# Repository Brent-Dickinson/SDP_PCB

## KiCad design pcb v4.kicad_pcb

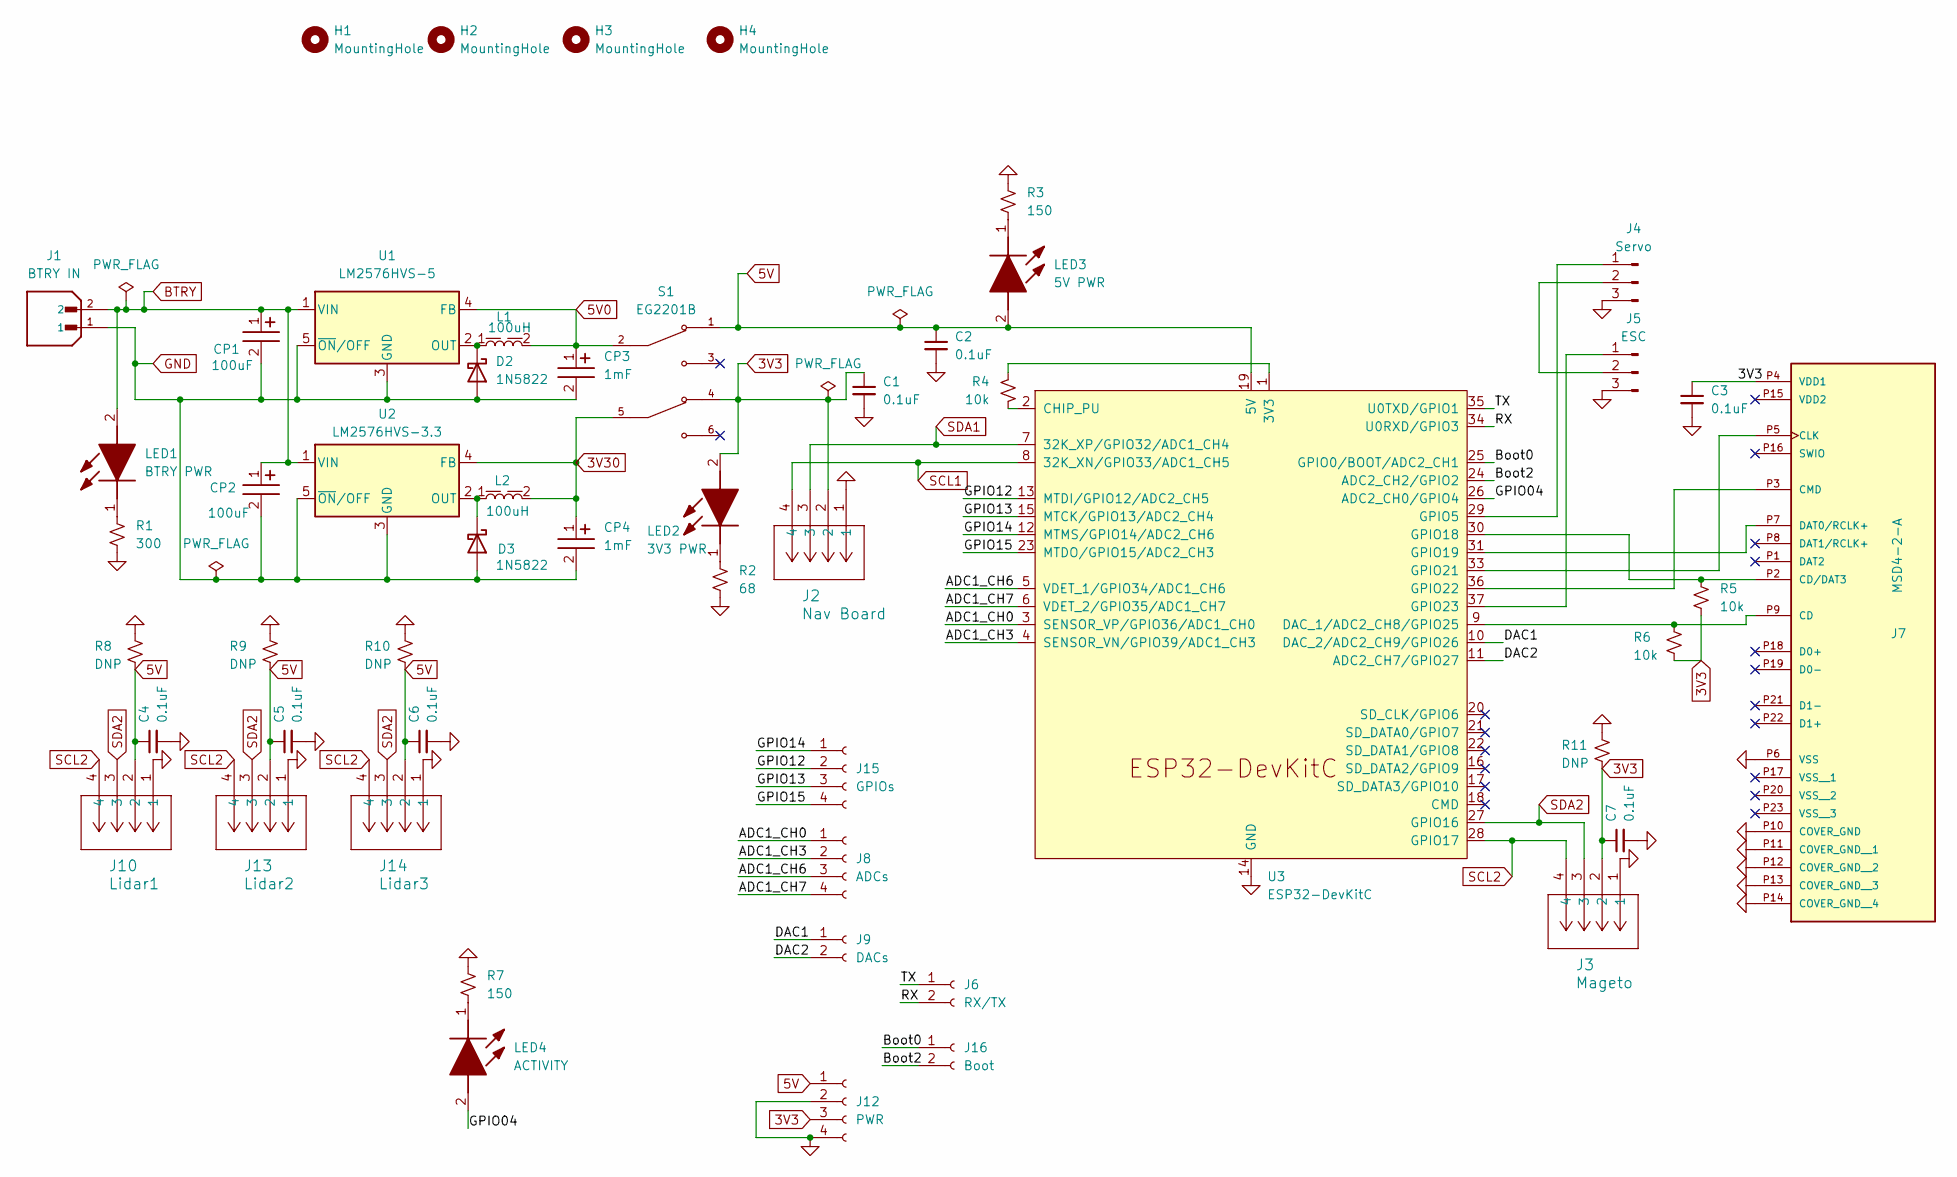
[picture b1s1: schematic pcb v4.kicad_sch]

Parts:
C1, C2, C3, C4, C5, C6, C7: 0.1uF; C_1206_3216Metric_Pad1.33x1.80mm_HandSolder
CP1, CP2: 100uF; CP_Wurth_WCAP-PSLP-D5L5.5; Part Number 875105242010
CP3, CP4: 1mF; CP_Wurth_WCAP-ASLI-D12.5L14; Part Number 865080462016
D2, D3: 1N5822; D_DO-201AD_P15.24mm_Horizontal
H1, H2, H3, H4: MountingHole; MountingHole_3.2mm_M3
J1: BTRY IN; JST_B2B-XH-A; PARTREV N/A
J2: Nav Board; CONN_SM04B-SRSS-TB_JST
J3: Mageto; CONN_SM04B-SRSS-TB_JST
J4: Servo; JST_XH_B3B-XH-A_1x03_P2.50mm_Vertical
J5: ESC; JST_XH_B3B-XH-A_1x03_P2.50mm_Vertical
J6: RX/TX; PinSocket_1x02_P2.54mm_Vertical
J7: MSD4-2-A; CUI_MSD4-2-A; PARTREV 1.0
J8: ADCs; PinSocket_1x04_P2.54mm_Vertical
J9: DACs; PinSocket_1x02_P2.54mm_Vertical
J10: Lidar1; CONN_SM04B-SRSS-TB_JST
J12: PWR; PinSocket_1x04_P2.54mm_Vertical
J13: Lidar2; CONN_SM04B-SRSS-TB_JST
J14: Lidar3; CONN_SM04B-SRSS-TB_JST
J15: GPIOs; PinSocket_1x04_P2.54mm_Vertical
J16: Boot; PinSocket_1x02_P2.54mm_Vertical
L1, L2: 100uH; L_Wurth_WE-PD-1245; Part Number 7447715101
LED1: BTRY PWR; LED_1206_3216Metric_Pad1.42x1.75mm_HandSolder; Mouser Part Number 638-EAST3215BA3
LED2: 3V3 PWR; LED_1206_3216Metric_Pad1.42x1.75mm_HandSolder; Mouser Part Number 638-EAST3215BA3
LED3: 5V PWR; LED_1206_3216Metric_Pad1.42x1.75mm_HandSolder; Mouser Part Number 638-EAST3215BA3
LED4: ACTIVITY; LED_1206_3216Metric_Pad1.42x1.75mm_HandSolder; Mouser Part Number 638-EAST3215BA3
R1: 300; R_1206_3216Metric_Pad1.30x1.75mm_HandSolder
R2: 68; R_1206_3216Metric_Pad1.30x1.75mm_HandSolder
R3, R7: 150; R_1206_3216Metric_Pad1.30x1.75mm_HandSolder
R4, R5, R6: 10k; R_1206_3216Metric_Pad1.30x1.75mm_HandSolder
R8, R9, R10, R11: DNP; R_1206_3216Metric_Pad1.30x1.75mm_HandSolder
S1: EG2201B; SW_EG2201B; PARTREV C
U1: LM2576HVS-5; TO-263-5_TabPin3
U2: LM2576HVS-3.3; TO-263-5_TabPin3
U3: ESP32-DevKitC

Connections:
3V3: C1.1, C3.1, C7.1, J2.2, J3.2, J7.P4 (VDD1), J12.3, LED2.2 (A), R5.2, R6.2, R11.2, S1.4
3V30: CP4.1, L2.2, S1.5, U2.4 (FB)
5V: C2.1, C4.1, C5.1, C6.1, J10.2, J12.1, J13.2, J14.2, LED3.2 (A), R8.2, R9.2, R10.2, S1.1, U3.19 (5V)
5V0: CP3.1, L1.2, S1.2, U1.4 (FB)
/ADC1_CH0: J8.1, U3.3 (SENSOR_VP/GPIO36/ADC1_CH0)
/ADC1_CH3: J8.2, U3.4 (SENSOR_VN/GPIO39/ADC1_CH3)
/ADC1_CH6: J8.3, U3.5 (VDET_1/GPIO34/ADC1_CH6)
/ADC1_CH7: J8.4, U3.6 (VDET_2/GPIO35/ADC1_CH7)
/Boot0: J16.1, U3.25 (GPIO0/BOOT/ADC2_CH1)
/Boot2: J16.2, U3.24 (ADC2_CH2/GPIO2)
/DAC1: J9.1, U3.10 (DAC_2/ADC2_CH9/GPIO26)
/DAC2: J9.2, U3.11 (ADC2_CH7/GPIO27)
/GPIO04: LED4.2 (A), U3.26 (ADC2_CH0/GPIO4)
/GPIO12: J15.2, U3.13 (MTDI/GPIO12/ADC2_CH5)
/GPIO13: J15.3, U3.15 (MTCK/GPIO13/ADC2_CH4)
/GPIO14: J15.1, U3.12 (MTMS/GPIO14/ADC2_CH6)
/GPIO15: J15.4, U3.23 (MTDO/GPIO15/ADC2_CH3)
/RX: J6.2, U3.34 (U0RXD/GPIO3)
/TX: J6.1, U3.35 (U0TXD/GPIO1)
BTRY: CP1.1, CP2.1, J1.2, LED1.2 (A), U1.1 (VIN), U2.1 (VIN)
GND: C1.2, C2.2, C3.2, C4.2, C5.2, C6.2, C7.2, CP1.2, CP2.2, CP3.2, CP4.2, D2.2 (A), D3.2 (A), J1.1, J2.1, J3.1, J4.3, J5.3, J7.P6 (VSS), J7.P10 (COVER_GND), J7.P11 (COVER_GND__1), J7.P12 (COVER_GND__2), J7.P13 (COVER_GND__3), J7.P14 (COVER_GND__4), J10.1, J12.2, J12.4, J13.1, J14.1, R1.2, R2.2, R3.2, R7.2, R8.1, R9.1, R10.1, R11.1, U1.3 (GND), U1.5 (~ON/OFF), U2.3 (GND), U2.5 (~ON/OFF), U3.14 (GND), U3.32 (GND), U3.38 (GND)
unnamed: D2.1 (K), L1.1, U1.2 (OUT)
unnamed: D3.1 (K), L2.1, U2.2 (OUT)
unnamed: J4.1, U3.29 (GPIO5)
unnamed: J4.2, J5.2
unnamed: J5.1, U3.37 (GPIO23)
unnamed: J7.P9 (CD), R6.1, U3.9 (DAC_1/ADC2_CH8/GPIO25)
unnamed: J7.P2 (CD/DAT3), R5.1, U3.30 (GPIO18)
unnamed: J7.P5 (CLK), U3.33 (GPIO21)
unnamed: J7.P3 (CMD), U3.36 (GPIO22)
unnamed: J7.P7 (DAT0/RCLK+), U3.31 (GPIO19)
unnamed: LED1.1 (K), R1.1
unnamed: LED2.1 (K), R2.1
unnamed: LED3.1 (K), R3.1
unnamed: LED4.1 (K), R7.1
unnamed: R4.1, U3.1 (3V3)
unnamed: R4.2, U3.2 (CHIP_PU)
SCL1: J2.4, U3.8 (32K_XN/GPIO33/ADC1_CH5)
SCL2: J3.4, J10.4, J13.4, J14.4, U3.28 (GPIO17)
SDA1: J2.3, U3.7 (32K_XP/GPIO32/ADC1_CH4)
SDA2: J3.3, J10.3, J13.3, J14.3, U3.27 (GPIO16)

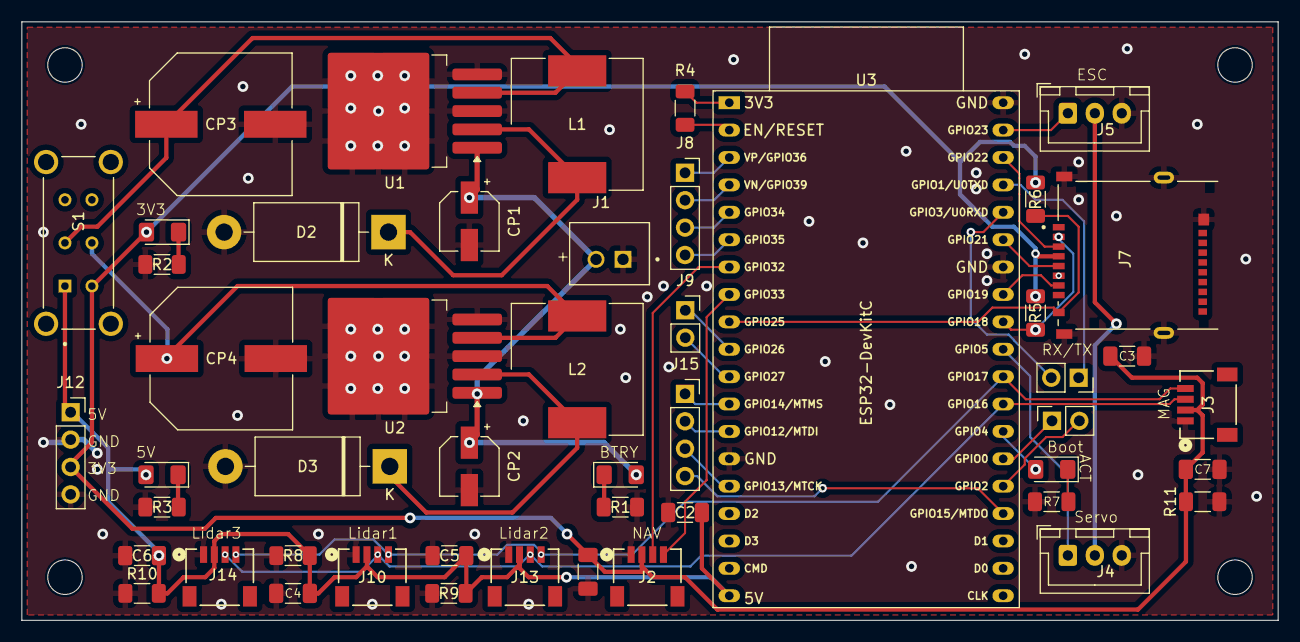
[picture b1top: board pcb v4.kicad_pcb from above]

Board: 2 copper layers, 116.5 x 55.5 mm, 53 parts (0 on the bottom side), 41 nets.

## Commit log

2025-03-20 updated gitignore
